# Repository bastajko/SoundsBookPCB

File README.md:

Project relies on ScottoKeebs libraries.

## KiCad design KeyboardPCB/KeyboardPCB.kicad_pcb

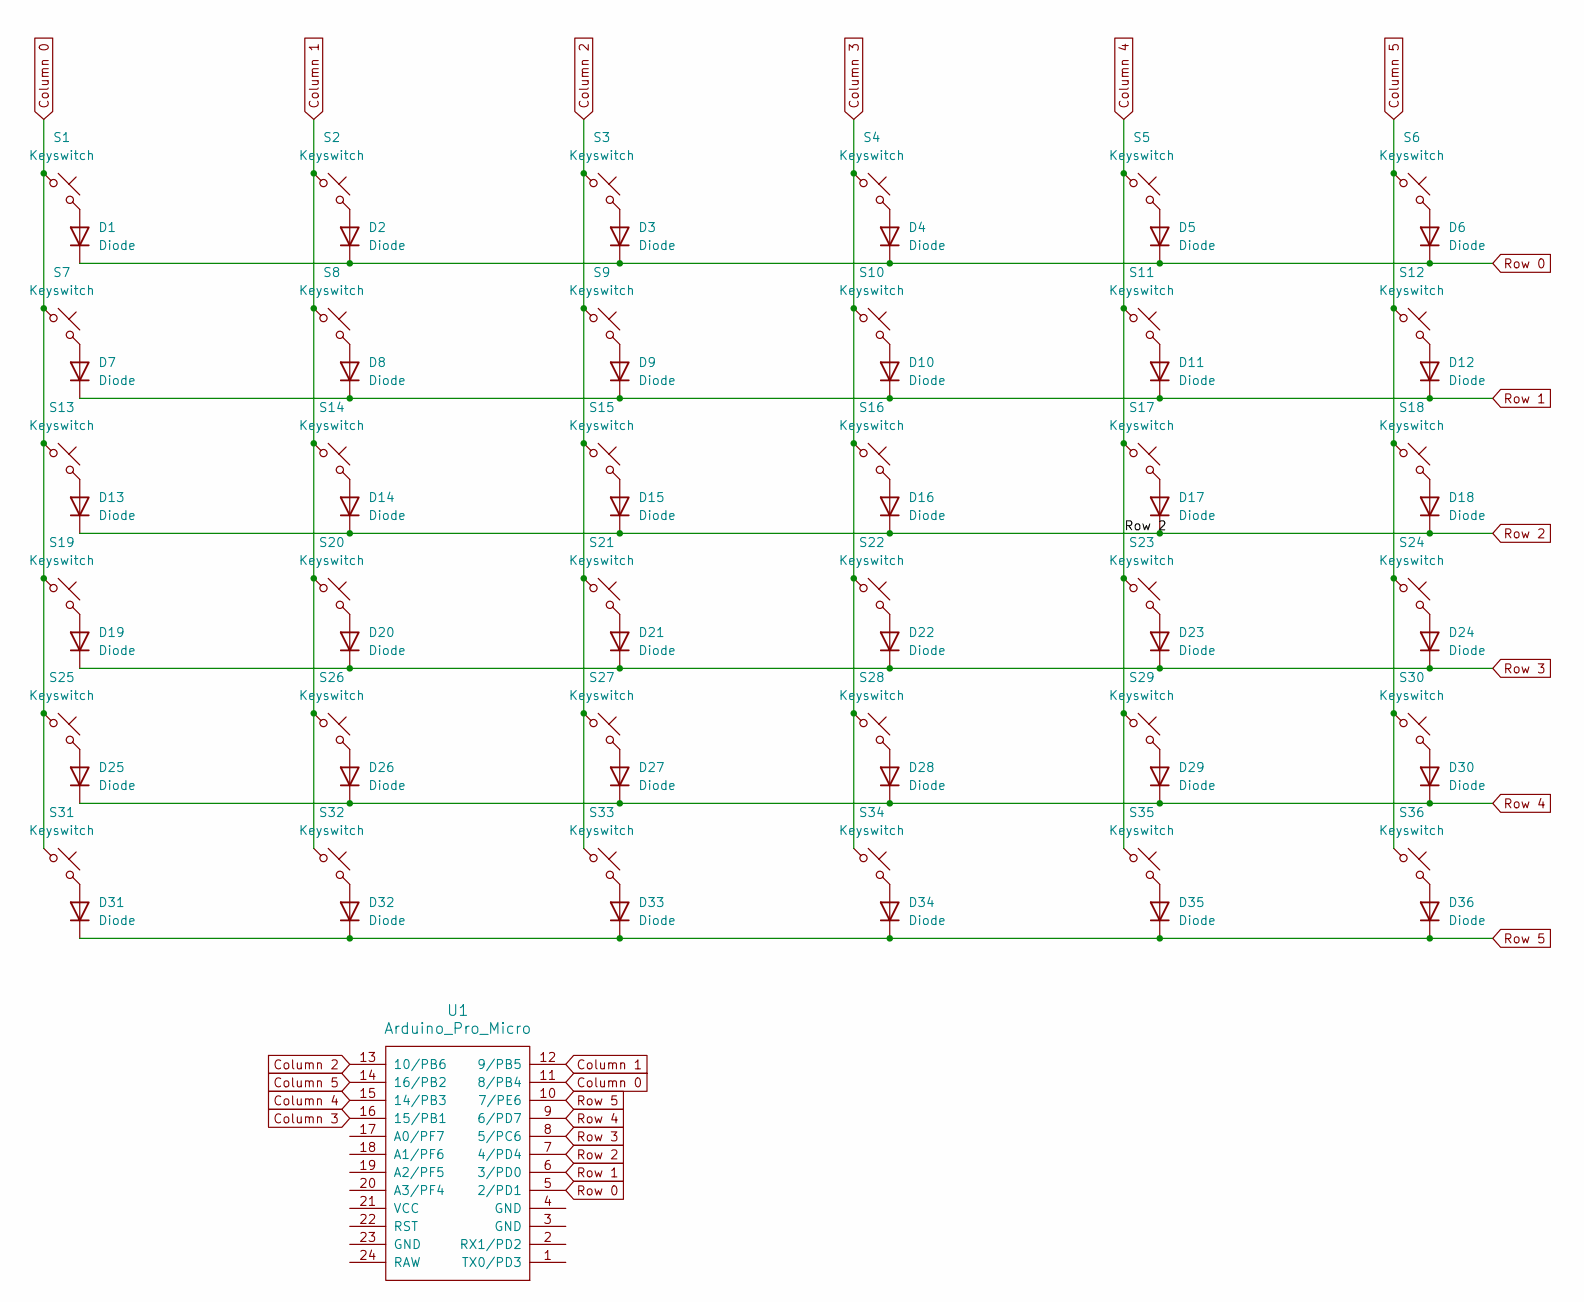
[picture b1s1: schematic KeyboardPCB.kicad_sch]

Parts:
D1, D2, D3, D4, D5, D6, D7, D8, D9, D10, D11, D12, D13, D14, D15, D16, D17, D18, D19, D20, D21, D22, D23, D24, D25, D26, D27, D28, D29, D30, D31, D32, D33, D34, D35, D36: Diode; Diode_DO-35
S1, S2, S3, S4, S5, S6, S7, S8, S9, S10, S11, S12, S13, S14, S15, S16, S17, S18, S19, S20, S21, S22, S23, S24, S25, S26, S27, S28, S29, S30, S31, S32, S33, S34, S35, S36: Keyswitch; SW_PUSH-WITHCAP-12mm
U1: Arduino_Pro_Micro

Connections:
Column 0: S1.1, S7.1, S13.1, S19.1, S25.1, S31.1, U1.11 (8/PB4)
Column 1: S2.1, S8.1, S14.1, S20.1, S26.1, S32.1, U1.12 (9/PB5)
Column 2: S3.1, S9.1, S15.1, S21.1, S27.1, S33.1, U1.13 (10/PB6)
Column 3: S4.1, S10.1, S16.1, S22.1, S28.1, S34.1, U1.16 (15/PB1)
Column 5: S6.1, S12.1, S18.1, S24.1, S30.1, S36.1, U1.14 (16/PB2)
unnamed: D1.2 (A), S1.2
unnamed: D2.2 (A), S2.2
unnamed: D3.2 (A), S3.2
unnamed: D4.2 (A), S4.2
unnamed: D5.2 (A), S5.2
unnamed: D6.2 (A), S6.2
unnamed: D7.2 (A), S7.2
unnamed: D8.2 (A), S8.2
unnamed: D9.2 (A), S9.2
unnamed: D10.2 (A), S10.2
unnamed: D11.2 (A), S11.2
unnamed: D12.2 (A), S12.2
unnamed: D13.2 (A), S13.2
unnamed: D14.2 (A), S14.2
unnamed: D15.2 (A), S15.2
unnamed: D16.2 (A), S16.2
unnamed: D17.2 (A), S17.2
unnamed: D18.2 (A), S18.2
unnamed: D19.2 (A), S19.2
unnamed: D20.2 (A), S20.2
unnamed: D21.2 (A), S21.2
unnamed: D22.2 (A), S22.2
unnamed: D23.2 (A), S23.2
unnamed: D24.2 (A), S24.2
unnamed: D25.2 (A), S25.2
unnamed: D26.2 (A), S26.2
unnamed: D27.2 (A), S27.2
unnamed: D28.2 (A), S28.2
unnamed: D29.2 (A), S29.2
unnamed: D30.2 (A), S30.2
unnamed: D31.2 (A), S31.2
unnamed: D32.2 (A), S32.2
unnamed: D33.2 (A), S33.2
unnamed: D34.2 (A), S34.2
unnamed: D35.2 (A), S35.2
unnamed: D36.2 (A), S36.2
Row 0: D1.1 (K), D2.1 (K), D3.1 (K), D4.1 (K), D5.1 (K), D6.1 (K), U1.5 (2/PD1)
Row 1: D7.1 (K), D8.1 (K), D9.1 (K), D10.1 (K), D11.1 (K), D12.1 (K), U1.6 (3/PD0)
Row 3: D19.1 (K), D20.1 (K), D21.1 (K), D22.1 (K), D23.1 (K), D24.1 (K), U1.8 (5/PC6)
Row 4: D25.1 (K), D26.1 (K), D27.1 (K), D28.1 (K), D29.1 (K), D30.1 (K), U1.9 (6/PD7)
Row 5: D31.1 (K), D32.1 (K), D33.1 (K), D34.1 (K), D35.1 (K), D36.1 (K), U1.10 (7/PE6)

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
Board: 2 copper layers, 73 parts (31 on the bottom side), 48 nets, no tracks yet.

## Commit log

2025-05-12 Creating PCB for sound book for Children
2025-05-12 Update in PCB editor
2025-05-13 Adding push button with caps 3D model
2025-05-13 Arranging button positions
